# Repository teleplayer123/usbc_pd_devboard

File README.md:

### Description
A development board to experiment with USB-C PD via an STM32 and FUSB302. 

The [PD Logger](firmware/pd_logger) firmware logs PD messages, attach/dettach events, CC voltage/orientation, and VBUS voltage. 
Connect to the board through UART and use a serial terminal to interact with 
the FUSB302 over I2C via the STM32F0. Logs will start showing once a PD capable device is detected.
A debug console menu can be accessed by pressing Enter in the terminal allowing direct writes and
reads to the FUSB302. Press "q" to exit the debug console and return to live logging.

### Dev Board

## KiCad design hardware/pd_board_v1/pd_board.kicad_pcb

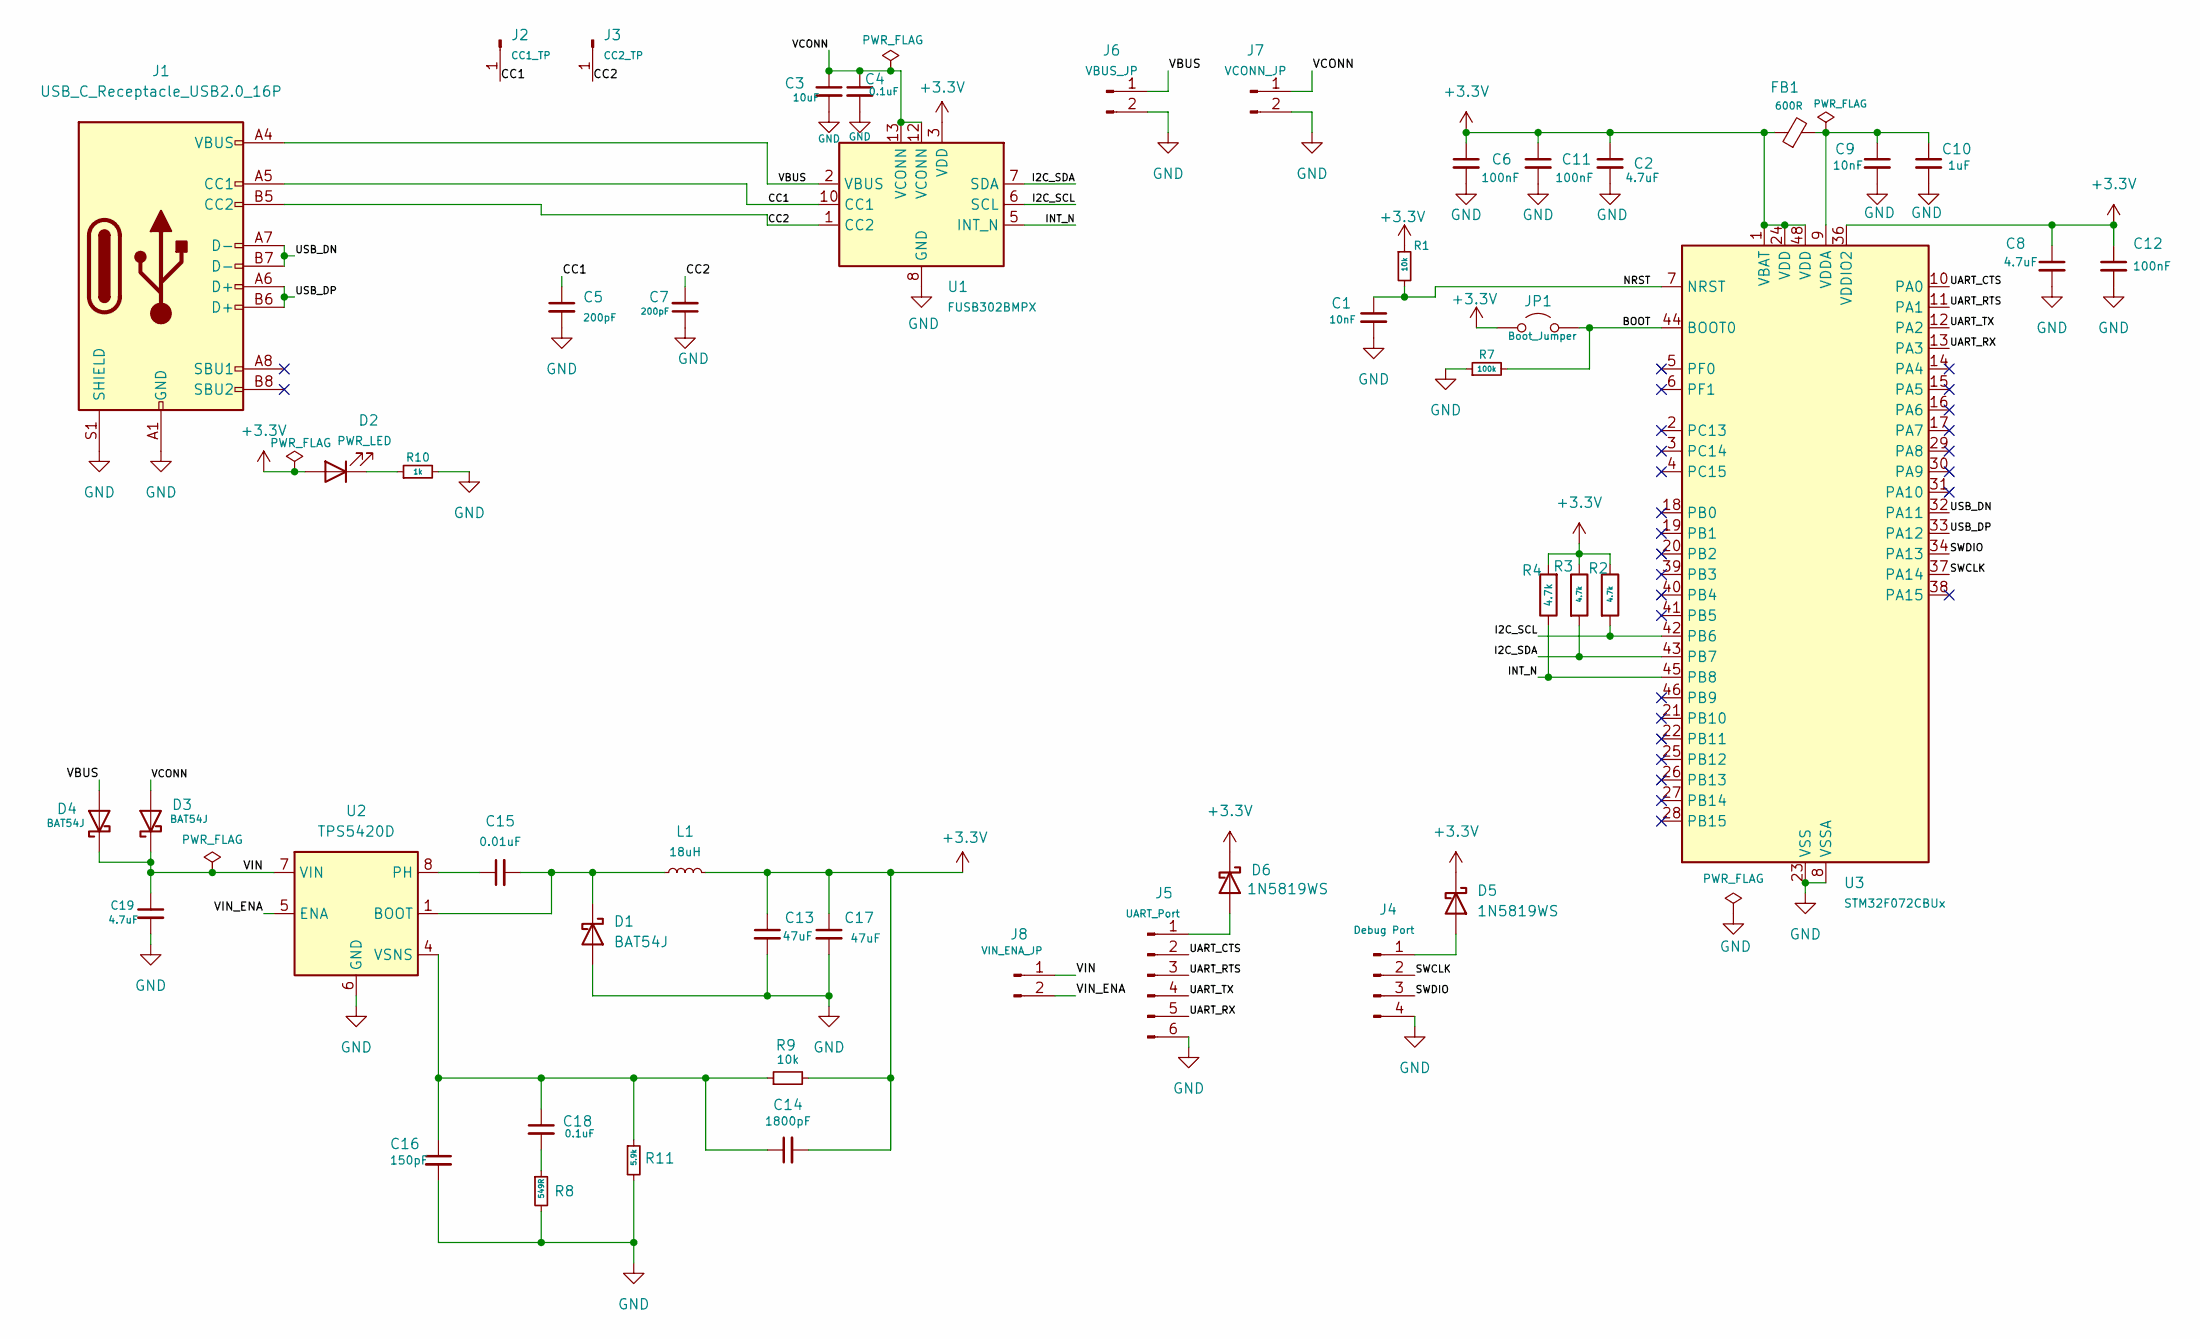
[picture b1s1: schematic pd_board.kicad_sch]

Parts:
C1, C9: 10nF; C_0402_1005Metric
C2, C8, C19: 4.7uF; C_0603_1608Metric
C3: 10uF; C_0603_1608Metric
C4: 0.1uF; C_0402_1005Metric
C5, C7: 200pF; C_0402_1005Metric
C6, C11, C12: 100nF; C_0402_1005Metric
C10: 1uF; C_0603_1608Metric
C13, C17: 47uF; C_0805_2012Metric
C14: 1800pF; C_0402_1005Metric
C15: 0.01uF; C_0402_1005Metric
C16: 150pF; C_0402_1005Metric
C18: 0.1uF; C_0603_1608Metric
D1, D3, D4: BAT54J; D_SOD-323F
D2: PWR_LED; LED_0402_1005Metric
D5, D6: 1N5819WS; D_SOD-323
FB1: 600R; L_0402_1005Metric
J1: USB_C_Receptacle_USB2.0_16P; USB_C_Receptacle_HCTL_HC-TYPE-C-16P-01A
J2: CC1_TP; PinHeader_1x01_P2.54mm_Vertical
J3: CC2_TP; PinHeader_1x01_P2.54mm_Vertical
J4: Debug Port; PinHeader_1x04_P2.54mm_Vertical
J5: UART_Port; PinHeader_1x06_P2.54mm_Vertical
J6: VBUS_JP; PinHeader_1x02_P2.54mm_Vertical
J7: VCONN_JP; PinHeader_1x02_P2.54mm_Vertical
J8: VIN_ENA_JP; PinHeader_1x02_P2.54mm_Vertical
JP1: Boot_Jumper; PinHeader_1x02_P2.54mm_Vertical
L1: 18uH; L_1008_2520Metric
R1, R9: 10k; R_0402_1005Metric
R2, R3, R4: 4.7k; R_0402_1005Metric
R7: 100k; R_0603_1608Metric
R8: 549R; R_0402_1005Metric
R10: 1k; R_0402_1005Metric
R11: 5.9k; R_0402_1005Metric
U1: FUSB302BMPX; WQFN-14-1EP_2.5x2.5mm_P0.5mm_EP1.45x1.45mm
U2: TPS5420D; SOIC-8_3.9x4.9mm_P1.27mm
U3: STM32F072CBUx; QFN-48-1EP_7x7mm_P0.5mm_EP5.6x5.6mm

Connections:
+3.3V: C2.1, C6.1, C8.1, C11.1, C12.1, C13.1, C14.2, C17.1, D2.2 (A), D5.1 (K), D6.1 (K), FB1.1, JP1.1 (A), L1.2, R1.1, R2.1, R3.1, R4.2, R9.2, U1.3 (VDD), U1.4 (VDD), U3.1 (VBAT), U3.24 (VDD), U3.36 (VDDIO2), U3.48 (VDD)
/BOOT: JP1.2 (B), R7.2, U3.44 (BOOT0)
/CC1: C5.1, J1.A5 (CC1), J2.1, U1.10 (CC1), U1.11 (CC1)
/CC2: C7.2, J1.B5 (CC2), J3.1, U1.1 (CC2), U1.14 (CC2)
/I2C_SCL: R2.2, U1.6 (SCL), U3.42 (PB6)
/I2C_SDA: R3.2, U1.7 (SDA), U3.43 (PB7)
/INT_N: R4.1, U1.5 (INT_N), U3.45 (PB8)
/NRST: C1.1, R1.2, U3.7 (NRST)
/SWCLK: J4.2, U3.37 (PA14)
/SWDIO: J4.3, U3.34 (PA13)
/UART_CTS: J5.2, U3.10 (PA0)
/UART_RTS: J5.3, U3.11 (PA1)
/UART_RX: J5.5, U3.13 (PA3)
/UART_TX: J5.4, U3.12 (PA2)
/USB_DN: J1.A7 (D-), J1.B7 (D-), U3.32 (PA11)
/USB_DP: J1.A6 (D+), J1.B6 (D+), U3.33 (PA12)
/VBUS: D4.2 (A), J1.A4 (VBUS), J1.A9 (VBUS), J1.B4 (VBUS), J1.B9 (VBUS), J6.1, U1.2 (VBUS)
/VCONN: C3.1, C4.1, D3.2 (A), J7.1, U1.12 (VCONN), U1.13 (VCONN)
/VIN: C19.1, D3.1 (K), D4.1 (K), J8.1, U2.7 (VIN)
/VIN_ENA: J8.2, U2.5 (ENA)
GND: C1.2, C2.2, C3.2, C4.2, C5.2, C6.2, C7.1, C8.2, C9.2, C10.2, C11.2, C12.2, C13.2, C16.2, C17.2, C19.2, D1.2 (A), J1.A1 (GND), J1.A12 (GND), J1.B1 (GND), J1.B12 (GND), J1.S1 (SHIELD), J4.4, J5.6, J6.2, J7.2, R7.1, R8.2, R10.2, R11.2, U1.8 (GND), U1.9 (GND), U1.15 (GND), U2.6 (GND), U3.8 (VSSA), U3.23 (VSS), U3.35 (VSS), U3.47 (VSS), U3.49 (VSS)
unnamed: C18.2, R8.1
unnamed: C15.2, D1.1 (K), L1.1, U2.1 (BOOT)
unnamed: D2.1 (K), R10.1
unnamed: D5.2 (A), J4.1
unnamed: D6.2 (A), J5.1
unnamed: C15.1, U2.8 (PH)
unnamed: C14.1, C16.1, C18.1, R9.1, R11.1, U2.4 (VSNS)
unnamed: C9.1, C10.1, FB1.2, U3.9 (VDDA)

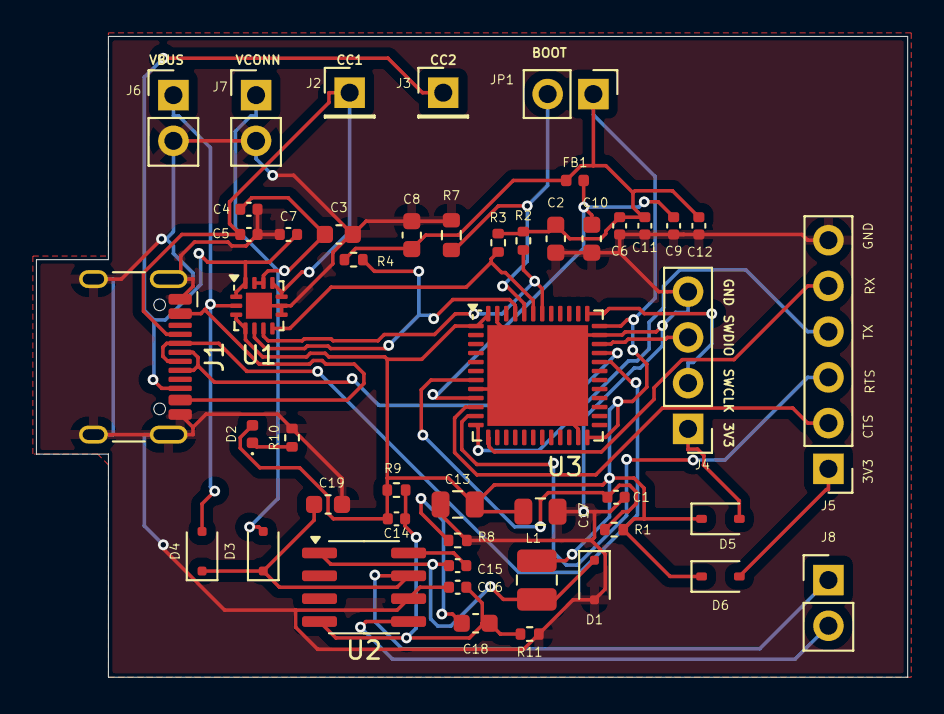
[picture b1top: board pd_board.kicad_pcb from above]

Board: 2 copper layers, 48.4 x 35.6 mm, 48 parts (0 on the bottom side), 29 nets.

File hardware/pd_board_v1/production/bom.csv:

Designator,Footprint,Quantity,Value,LCSC Part #
"C1, C9",0402,2,10nF,
C10,0603,1,1uF,
"C11, C12, C6",0402,3,100nF,
"C13, C17",0805,2,47uF,
C14,0402,1,1800pF,
C15,0402,1,0.01uF,
C16,0402,1,150pF,
C18,0603,1,0.1uF,
"C19, C2, C8",0603,3,4.7uF,
C3,0603,1,10uF,
C4,0402,1,0.1uF,
"C5, C7",0402,2,200pF,
"D1, D3, D4",D_SOD-323F,3,BAT54J,
D2,0402,1,PWR_LED,
"D5, D6",D_SOD-323,2,1N5819WS,
FB1,0402,1,600R,
J1,USB_C_Receptacle_HCTL_HC-TYPE-C-16P-01A,1,USB_C_Receptacle_USB2.0_16P,
J2,PinHeader_1x01_P2.54mm_Vertical,1,CC1_TP,
J3,PinHeader_1x01_P2.54mm_Vertical,1,CC2_TP,
J4,PinHeader_1x04_P2.54mm_Vertical,1,Debug Port,
J5,PinHeader_1x06_P2.54mm_Vertical,1,UART_Port,
J6,PinHeader_1x02_P2.54mm_Vertical,1,VBUS_JP,
J7,PinHeader_1x02_P2.54mm_Vertical,1,VCONN_JP,
J8,PinHeader_1x02_P2.54mm_Vertical,1,VIN_ENA_JP,
JP1,PinHeader_1x02_P2.54mm_Vertical,1,Boot_Jumper,
L1,1008,1,18uH,
"R1, R9",0402,2,10k,
R10,0402,1,1k,
R11,0402,1,5.9k,
"R2, R3, R4",0402,3,4.7k,
R7,0603,1,100k,
R8,0402,1,549R,
U1,WQFN-14-1EP_2.5x2.5mm_P0.5mm_EP1.45x1.45mm,1,FUSB302BMPX,
U2,SOIC-8_3.9x4.9mm_P1.27mm,1,TPS5420D,
U3,QFN-48-1EP_7x7mm_P0.5mm_EP5.6x5.6mm,1,STM32F072CBUx,

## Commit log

2025-11-19 Add MIT License to the project
2026-01-24 Add USB CDC support in usb_help.c
